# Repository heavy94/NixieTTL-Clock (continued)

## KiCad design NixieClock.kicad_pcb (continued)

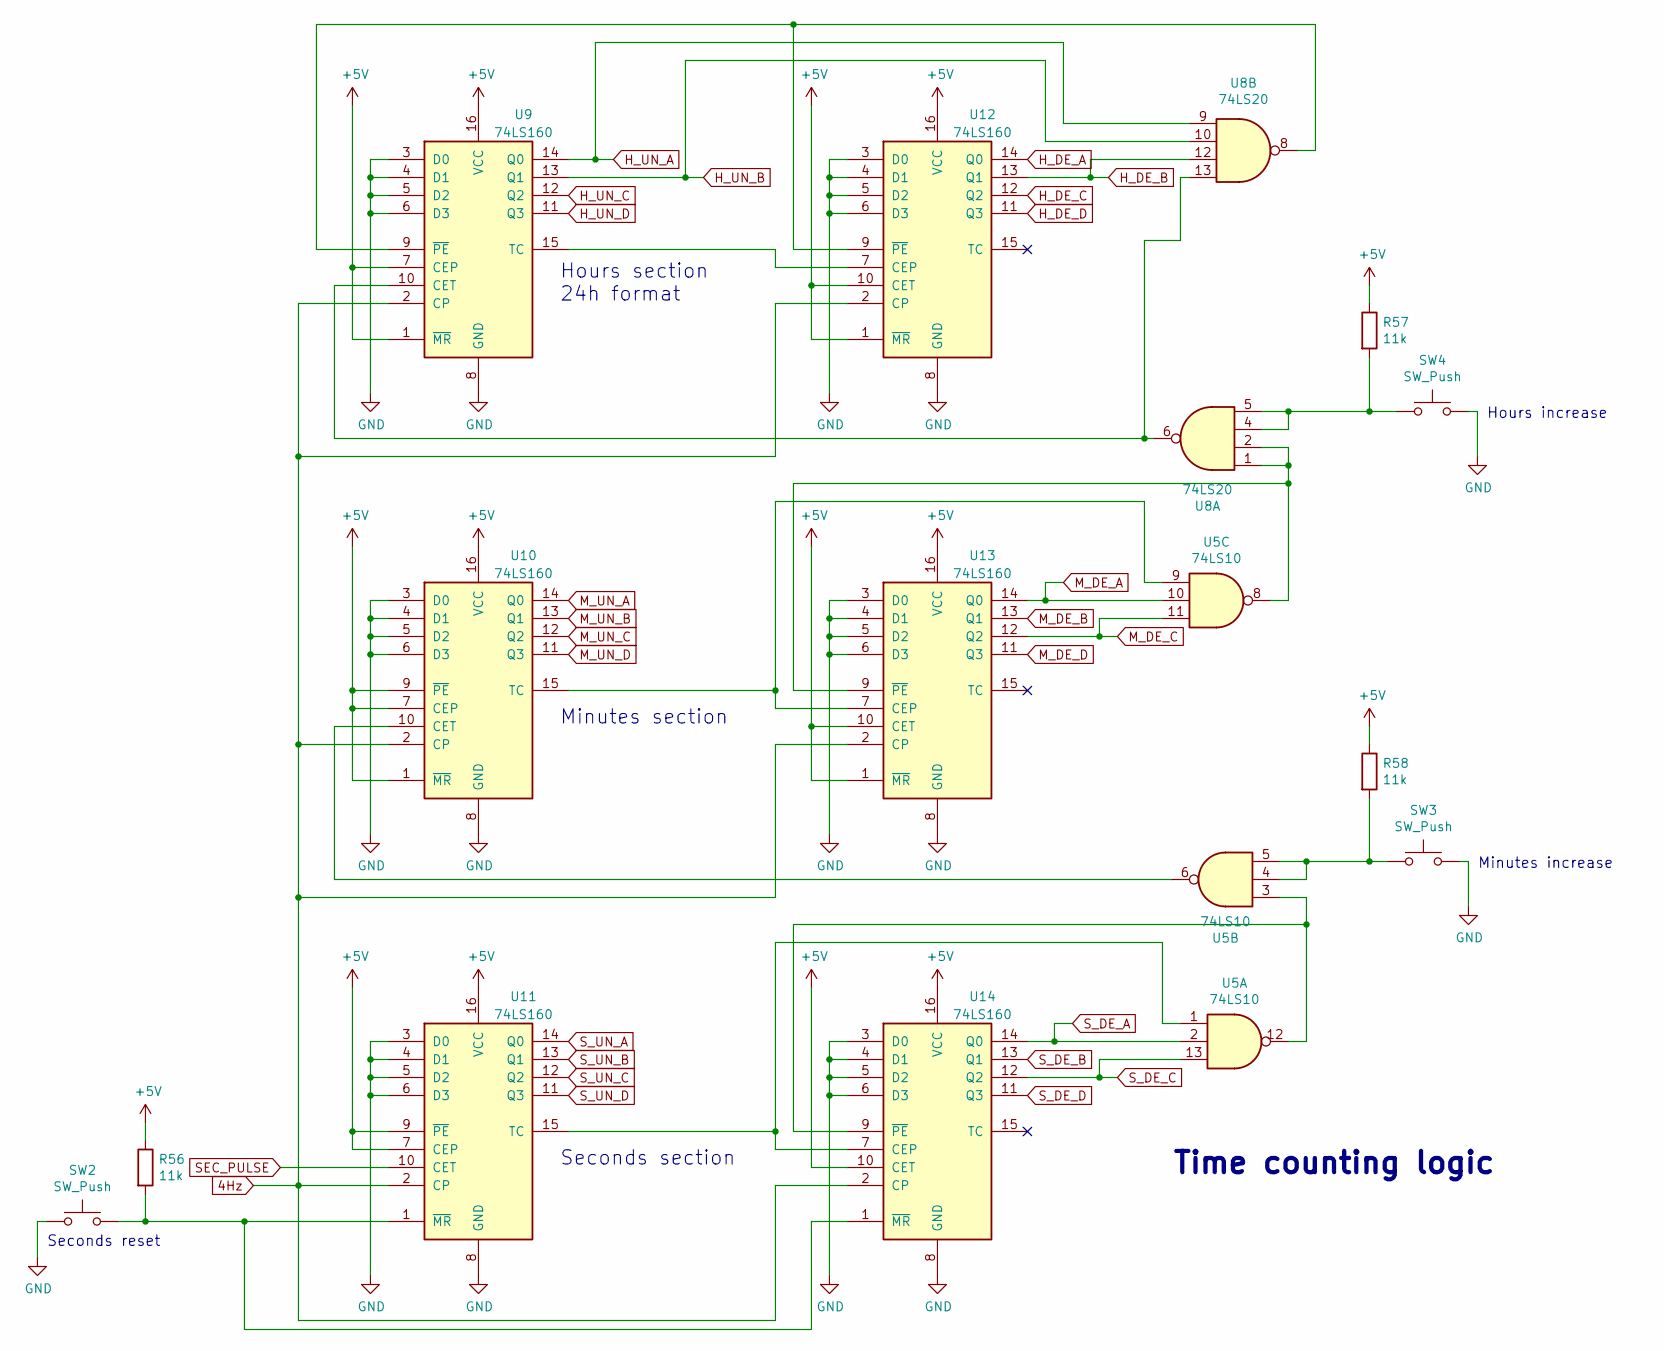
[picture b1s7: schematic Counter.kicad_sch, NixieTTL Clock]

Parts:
R56, R57, R58: 11k; R_Axial_DIN0207_L6.3mm_D2.5mm_P10.16mm_Horizontal
SW2, SW3, SW4: SW_Push; SW_Tactile_SPST_Angled_PTS645Vx83-2LFS
U5: 74LS10; DIP-14_W7.62mm
U8: 74LS20; DIP-14_W7.62mm
U9, U10, U11, U12, U13, U14: 74LS160; DIP-16_W7.62mm

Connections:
4Hz: U9.2 (CP), U10.2 (CP), U11.2 (CP), U12.2 (CP), U13.2 (CP), U14.2 (CP); also elsewhere on the board
+5V: R56.1, R57.1, R58.1, U9.1 (~MR), U9.7 (CEP), U9.16 (VCC), U10.1 (~MR), U10.7 (CEP), U10.9 (~PE), U10.16 (VCC), U11.7 (CEP), U11.9 (~PE), U11.16 (VCC), U12.1 (~MR), U12.10 (CET), U12.16 (VCC), U13.1 (~MR), U13.10 (CET), U13.16 (VCC), U14.10 (CET), U14.16 (VCC); also elsewhere on the board
GND: SW2.1, SW3.2, SW4.2, U9.3 (D0), U9.4 (D1), U9.5 (D2), U9.6 (D3), U9.8 (GND), U10.3 (D0), U10.4 (D1), U10.5 (D2), U10.6 (D3), U10.8 (GND), U11.3 (D0), U11.4 (D1), U11.5 (D2), U11.6 (D3), U11.8 (GND), U12.3 (D0), U12.4 (D1), U12.5 (D2), U12.6 (D3), U12.8 (GND), U13.3 (D0), U13.4 (D1), U13.5 (D2), U13.6 (D3), U13.8 (GND), U14.3 (D0), U14.4 (D1), U14.5 (D2), U14.6 (D3), U14.8 (GND); also elsewhere on the board
H_DE_A: U12.14 (Q0); also elsewhere on the board
H_DE_B: U8.12, U12.13 (Q1); also elsewhere on the board
H_DE_C: U12.12 (Q2); also elsewhere on the board
H_DE_D: U12.11 (Q3); also elsewhere on the board
H_UN_A: U8.9, U9.14 (Q0); also elsewhere on the board
H_UN_B: U8.10, U9.13 (Q1); also elsewhere on the board
H_UN_C: U9.12 (Q2); also elsewhere on the board
H_UN_D: U9.11 (Q3); also elsewhere on the board
M_DE_A: U5.10, U13.14 (Q0); also elsewhere on the board
M_DE_B: U13.13 (Q1); also elsewhere on the board
M_DE_C: U5.11, U13.12 (Q2); also elsewhere on the board
M_DE_D: U13.11 (Q3); also elsewhere on the board
M_UN_A: U10.14 (Q0); also elsewhere on the board
M_UN_B: U10.13 (Q1); also elsewhere on the board
M_UN_C: U10.12 (Q2); also elsewhere on the board
M_UN_D: U10.11 (Q3); also elsewhere on the board
unnamed: R56.2, SW2.2, U11.1 (~MR), U14.1 (~MR)
unnamed: R57.2, SW4.1, U8.4, U8.5
unnamed: R58.2, SW3.1, U5.4, U5.5
unnamed: U8.6, U8.13, U9.10 (CET)
unnamed: U5.6, U10.10 (CET)
unnamed: U5.9, U10.15 (TC), U13.7 (CEP)
unnamed: U5.1, U11.15 (TC), U14.7 (CEP)
unnamed: U9.15 (TC), U12.7 (CEP)
unnamed: U8.8, U9.9 (~PE), U12.9 (~PE)
unnamed: U5.8, U8.1, U8.2, U13.9 (~PE)
unnamed: U5.3, U5.12, U14.9 (~PE)
SEC_PULSE: U11.10 (CET); also elsewhere on the board
S_DE_A: U5.2, U14.14 (Q0); also elsewhere on the board
S_DE_B: U14.13 (Q1); also elsewhere on the board
S_DE_C: U5.13, U14.12 (Q2); also elsewhere on the board
S_DE_D: U14.11 (Q3); also elsewhere on the board
S_UN_A: U11.14 (Q0); also elsewhere on the board
S_UN_B: U11.13 (Q1); also elsewhere on the board
S_UN_C: U11.12 (Q2); also elsewhere on the board
S_UN_D: U11.11 (Q3); also elsewhere on the board

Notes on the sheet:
Time counting logic
Seconds reset
Hours increase
Minutes section
Hours section 24h format
Minutes increase
Seconds section

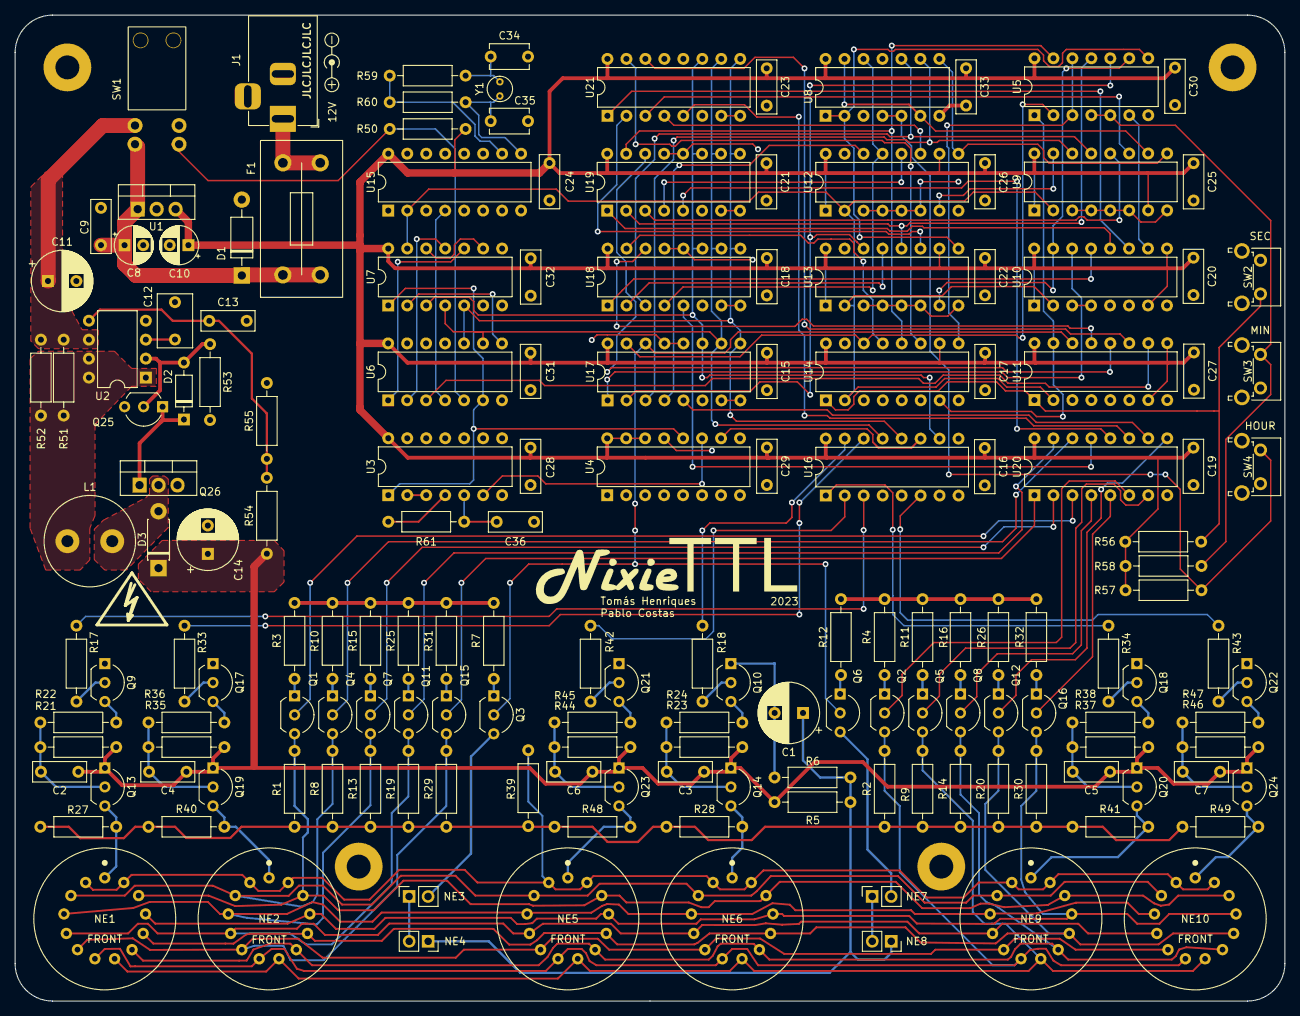
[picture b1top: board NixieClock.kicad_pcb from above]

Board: 2 copper layers, 170.0 x 132.0 mm, 166 parts (0 on the bottom side), 140 nets.

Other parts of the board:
12V: Symbol_Barrel_Polarity
NE7, NE8: INS-1; PinSocket_1x02_P2.54mm_Vertical
NE9, NE10: IN-14

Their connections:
A5: NE9.1 (A); also elsewhere on the board
A6: NE10.1 (A); also elsewhere on the board
CS2_K: NE7.2 (K); also elsewhere on the board
CS_A: NE8.1 (A); also elsewhere on the board
K0: NE9.12 (K0), NE10.12 (K0); also elsewhere on the board
K1: NE9.3 (K1), NE10.3 (K1); also elsewhere on the board
K2: NE9.4 (K2), NE10.4 (K2); also elsewhere on the board
K3: NE9.5 (K3), NE10.5 (K3); also elsewhere on the board
K4: NE9.6 (K4), NE10.6 (K4); also elsewhere on the board
K5: NE9.7 (K5), NE10.7 (K5); also elsewhere on the board
K6: NE9.8 (K6), NE10.8 (K6); also elsewhere on the board
K7: NE9.9 (K7), NE10.9 (K7); also elsewhere on the board
K8: NE9.10 (K8), NE10.10 (K8); also elsewhere on the board
K9: NE9.11 (K9), NE10.11 (K9); also elsewhere on the board
KDP: NE9.2 (KPL), NE9.13 (KPR), NE10.2 (KPL), NE10.13 (KPR); also elsewhere on the board
unnamed: NE7.1 (A), NE8.2 (K)

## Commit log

2021-01-14 Upload original design idea
2022-02-25 Design moved to KiCad 6, counter logic fixed, extra display connector removed
2023-03-04 layout started
2023-04-01 Layout completed
2023-04-09 Pablo's review, several changes:
    Schematic:
    - Overall aesthetics
    - Added PWR_FLAG to remove ERC errors.
    Layout:
    - Overall component alignment
    - Removed some loops and unnecessary vias.
2023-04-09 routed
2023-04-09 DRC 0k
2023-04-15 Implemented changes from pablo_cambios branch. Generated Gerbers
